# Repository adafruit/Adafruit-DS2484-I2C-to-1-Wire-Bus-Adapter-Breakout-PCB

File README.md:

## Adafruit DS2484 I2C to 1-Wire Bus Adapter Breakout - STEMMA QT / Qwiic JST SH 1mm PCB

<a href="http://www.adafruit.com/products/5976"><br/>
Click here to purchase one from the Adafruit shop</a>

PCB files for the Adafruit DS2484 I2C to 1-Wire Bus Adapter Breakout - STEMMA QT / Qwiic JST SH 1mm. 

Format is EagleCAD schematic and board layout
* https://www.adafruit.com/product/5976

### Description

By customer request, this is a DS2484 Stemma QT board that uses a I2C-to-1W controller chip, with ESD protection and support for split supplies. You can easily connect it to an existing I2C bus and then use the screw terminals to attach multiple DS18B20's, or pair it with our 1-Wire chaining breakouts for fancier experimentation.

You're probably familiar with the 'top three' electronics protocols: I2C, SPI and UART. Perhaps you're aware of a fourth one, called "1-Wire" which was invented by Dallas Semiconductor (which became Maxim, which became Analog Devices). As you may expect, this protocol uses a single data wire plus a ground wire (and an optional power wire) to connect to any number of sensors or memory chips that all share the same bus.

In theory, there's a lot of different 1-Wire devices out there, but in reality almost everyone uses 1-Wire for DS18b20 temperature sensors. the long wire lengths and ease of 'chaining' by sharing a single bus wire makes it perfectly fine for this purpose. You can bit-bang 1-Wire on most microcontrollers, and some SBCs like Raspberry Pi have kernel module support. But are lots of chips or firmware stacks without 1-Wire capability, or maybe you want to use 1-Wire devices on your desktop computer or other SBC with I2C.

To get you going fast, we spun up a custom-made PCB in the STEMMA QT form factor, making it easy to interface with. The STEMMA QT connectors on either side are compatible with the SparkFun Qwiic I2C connectors. This allows you to make solderless connections between your development board and the DS2484 or to chain it with a wide range of other sensors and accessories using a compatible cable.

You can power the board directly from the STEMMA QT cable, whether it is 3V or 5V. If you want a different voltage on the 1-Wire power pin, cut the onboard trace and you can inject the voltage at the terminal block.

### License

Adafruit invests time and resources providing this open source design, please support Adafruit and open-source hardware by purchasing products from [Adafruit](https://www.adafruit.com)!

Designed by Limor Fried/Ladyada for Adafruit Industries.

Creative Commons Attribution/Share-Alike, all text above must be included in any redistribution. 
See license.txt for additional details.

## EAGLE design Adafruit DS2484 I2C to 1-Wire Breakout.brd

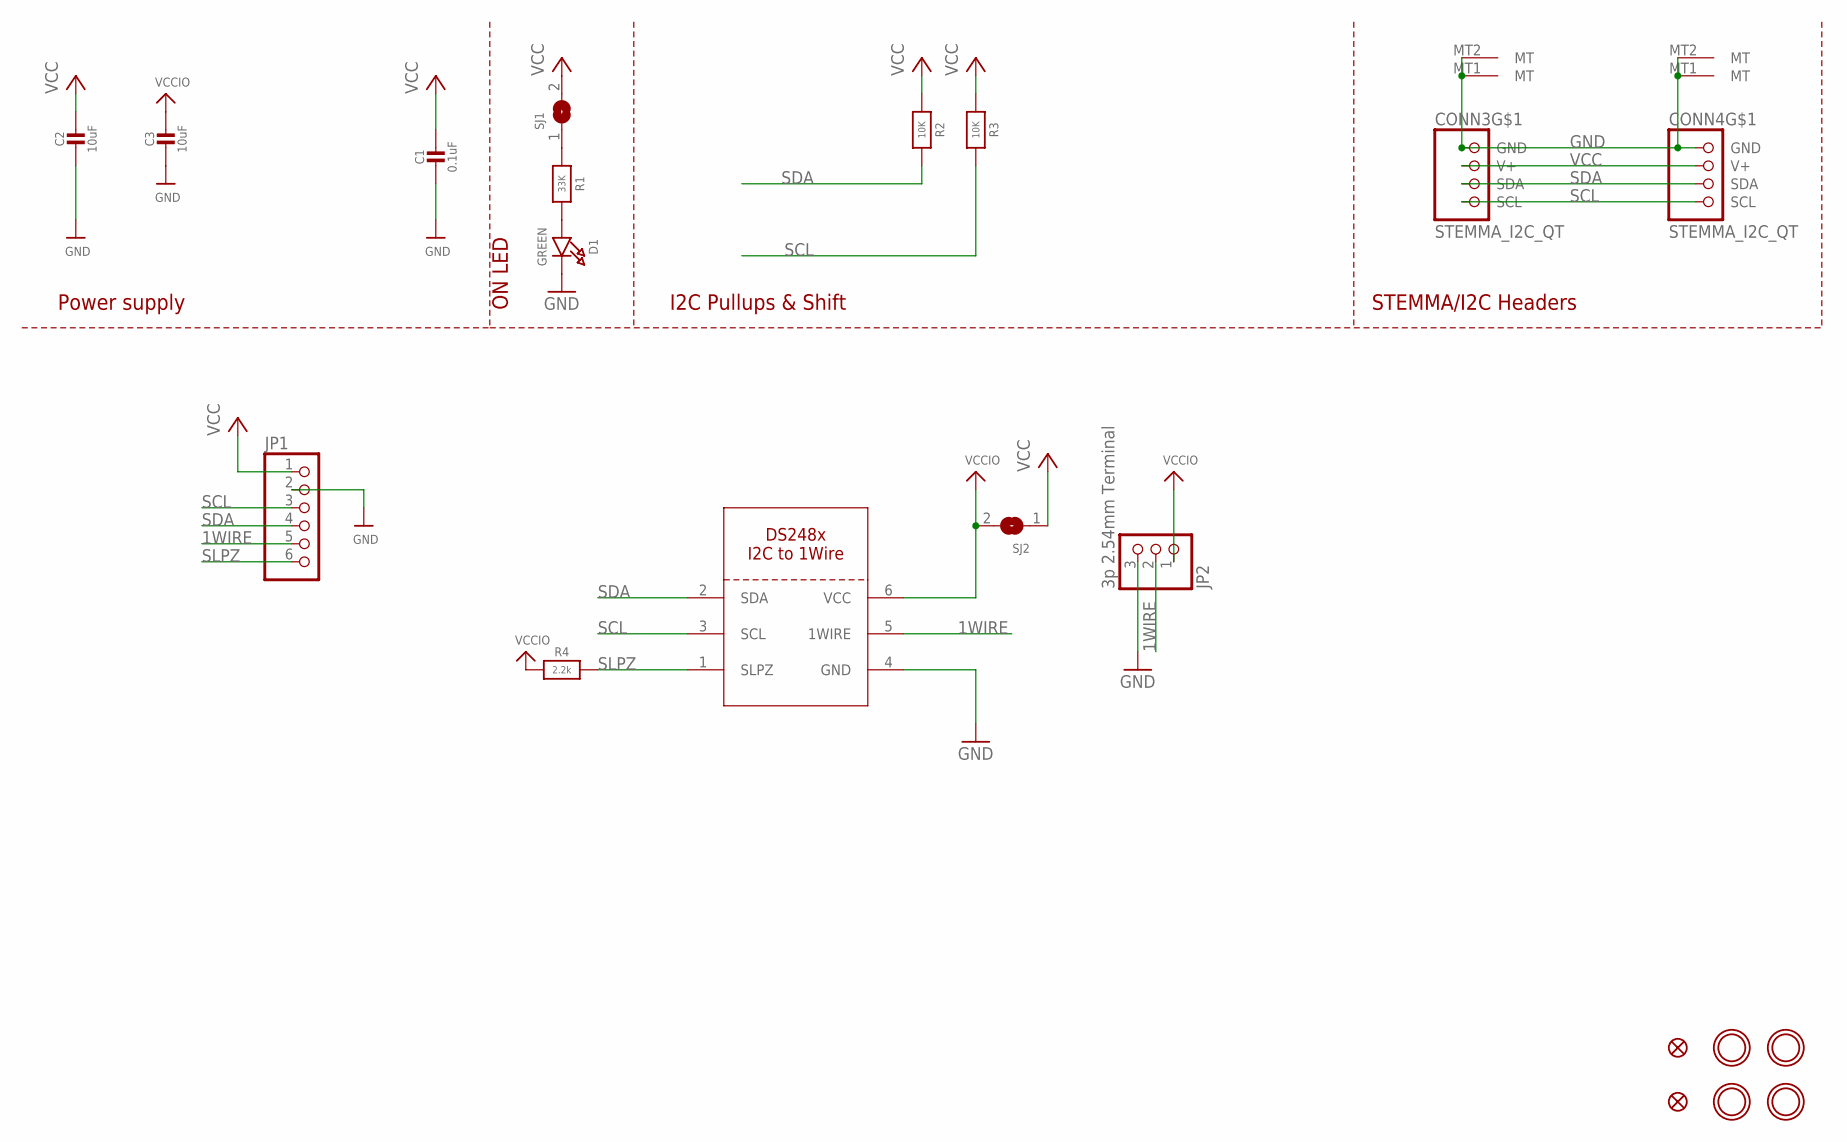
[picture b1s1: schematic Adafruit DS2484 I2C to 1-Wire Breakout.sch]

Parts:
C1: 0.1uF; 0603-NO
C2, C3: 10uF; 0805-NO
CONN3, CONN4: STEMMA_I2C_QT; JST_SH4
D1: GREEN; CHIPLED_0603_NOOUTLINE
FID3, FID4: FIDUCIAL_0.5MM
IC1: DS248XR; SOT23-6
JP1: HEADER-1X670MIL; 1X06_ROUND_70
JP2: 3p 2.54mm Terminal; 1X03_2.54MMTERMINAL
R1: 33K; 0603-NO
R2, R3: 10K; 0603-NO
R4: 2.2k; 0603-NO
SJ1, SJ2: SOLDERJUMPERCLOSED; SOLDERJUMPER_CLOSEDWIRE
U$1, U$17, U$19, U$21: MOUNTINGHOLE2.5; MOUNTINGHOLE_2.5_PLATED

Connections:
1WIRE: IC1.5 (1WIRE), JP1.5, JP2.2
GND: C1.2, C2.2, C3.2, CONN3.1 (GND), CONN3.MT1 (MT), CONN3.MT2 (MT), CONN4.1 (GND), CONN4.MT1 (MT), CONN4.MT2 (MT), D1.C, IC1.4 (GND), JP1.2, JP2.3
unnamed: D1.A, R1.2
unnamed: R1.1, SJ1.1
SCL: CONN3.4 (SCL), CONN4.4 (SCL), IC1.3 (SCL), JP1.3, R3.2
SDA: CONN3.3 (SDA), CONN4.3 (SDA), IC1.2 (SDA), JP1.4, R2.2
SLPZ: IC1.1 (SLPZ), JP1.6, R4.2
VCC: C1.1, C2.1, CONN3.2 (V+), CONN4.2 (V+), JP1.1, R2.1, R3.1, SJ1.2, SJ2.1
VCCIO: C3.1, IC1.6 (VCC), JP2.1, R4.1, SJ2.2

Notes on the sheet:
I2C Pullups & Shift
STEMMA/I2C Headers
ON LED
Power supply

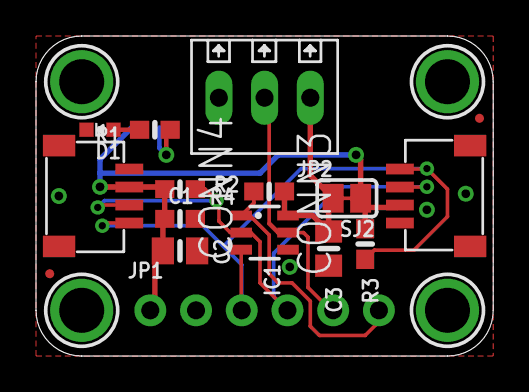
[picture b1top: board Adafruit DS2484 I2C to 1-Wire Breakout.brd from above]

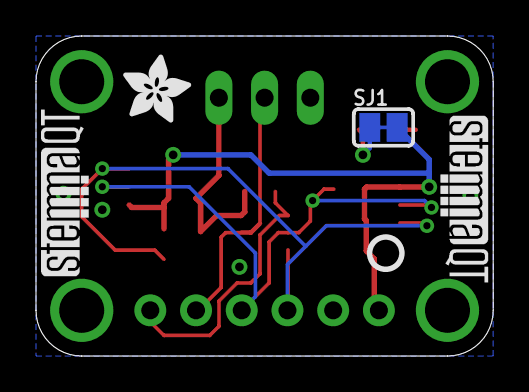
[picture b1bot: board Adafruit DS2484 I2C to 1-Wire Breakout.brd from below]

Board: 2 copper layers, 25.4 x 17.8 mm, 45 parts (13 on the bottom side), 9 nets.

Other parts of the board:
PLABEL0: PLABEL0
PLABEL1: PLABEL1
PLABEL2: PLABEL2
PLABEL3: PLABEL3
PLABEL4: PLABEL4
PLABEL5: PLABEL5
PLABEL6: PLABEL6
PLABEL7: PLABEL7
PLABEL8: PLABEL8
PLABEL9: PLABEL9
PLABEL10: PLABEL10
PLABEL11: PLABEL11
PLABEL12: PLABEL12
PLABEL13: PLABEL13
PLABEL14: PLABEL14
PLABEL15: PLABEL15
PLABEL16: PLABEL16
PLABEL17: PLABEL17
PLABEL18: PLABEL18
PLABEL19: PLABEL19
U$22: ADAFRUIT_3.5MM
U$25: PCBFEAT-REV-040
U$30, U$31: STEMMAQT

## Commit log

2024-06-13 cookiecutter

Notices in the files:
parts and their libraries:
microbuilder: This work is placed in the public domain, and may be freely used for commercial and non-commercial work with the following conditions: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
